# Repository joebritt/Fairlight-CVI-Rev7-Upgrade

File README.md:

# Fairlight-CVI-Rev7-Upgrade
Board set to upgrade a Rev5 Fairlight CVI to Rev7. This upgrade also eliminates the need for backup batteries.

See overview and installation guide [here](https://docs.google.com/document/d/1melksT-DwwU80pforqxVVXWFiSj0hJ2Gdj74KaH-A6M/edit?usp=sharing).

### All PCB designs were done in Eagle.

There are 4 different PCBs:</br>

One is the actual CVI06A, which mounts to the rear of the CVI. It is substantially smaller than the original CVI06.</br>

One is a small board which replaces the SRAM inside the CVI. This new board uses an FRAM to provide nonvolatile storage without a battery</br>

Two of these are just DIP-to-PLCC EPROM adapter boards.</br>
I made these because I had a bunch of PLCC 27C010 EPROMS I wanted to use! You can also just use 2716 and 27C128 EPROMs instead of these boards.

### EPROM Images

There are 4 EPROM images for inside the CVI unit. You'll replace the Rev5 EPROMs with parts programmed with these images:

CVI1R70.BIN and CVI2R70.BIN are images of Rev7 firmware EPROMs CVI1 and CVI2. These each go in a 27C128 16KB EPROM.

CVIHO52.BIN is the Horizonal timing control EPROM. This goes into a 2716 2KB EPROM.</br>
CVIVE50.BIN is the Vertical timing control EPROM. This goes into a 2716 2KB EPROM.

### PCB Designs

[27C128_adapter](https://oshpark.com/shared_projects/G9Li1LrF):</br>
Adapts a PLCC32 27C010 style memory to a DIP 27C128 style memory footprint.
Program just the bottom 16KB of the 27C010 before soldering it to the board.

[2716_adapter](https://oshpark.com/shared_projects/a2X7br2n):</br>
Adapts a PLCC32 27C010 style memory to a DIP 2716 style memory footprint.
Program just the bottom 2KB of the 27C010 before soldering it to the board.

[NoBattNVRAM](https://oshpark.com/shared_projects/FdYXVcIm):</br>
Replaces the CVI SRAM / 3V Lithium battery with FRAM. Nonvolatile memory, no battery needed.
A wire with a grabber clip is used to pick up the 6809 /E clock, which is needed to qualify accesses to the FRAM.

[CVI06A](https://oshpark.com/shared_projects/1o1eqgmB):</br>
The main attraction. Replacement for the original CVI06 expansion board. Smaller, easier to attach, and also uses FRAM for battery-free nonvolatile storage. Program the 27C010 for this board with the CVI43_CVI06A_v11 file in the low 32KB. This image contains the CVI3 and CVI4 Rev7 firmware EPROM images in a single part.

### Enclosure

CVI06A_box.stl and CVI06A_lid.stl can be 3D printed to make a small enclosure to protect the CVI06A PCB.</br>
The box is held together by friction. Note the capture features and line them up when closing.</br>
</br>
You can see the OnShape files used to create the enclosure box [here](https://cad.onshape.com/documents/24956ac0c366857a8c3e2111/w/adee8d27d6b88507ca310e0c/e/6c70102fddee723f7350afbb) and top [here](https://cad.onshape.com/documents/769b7af279cff9270446b3d7/w/f598dc3f7b092dcb1121a7f3/e/3ff1c2d9f7cff27cb58aa0f2).

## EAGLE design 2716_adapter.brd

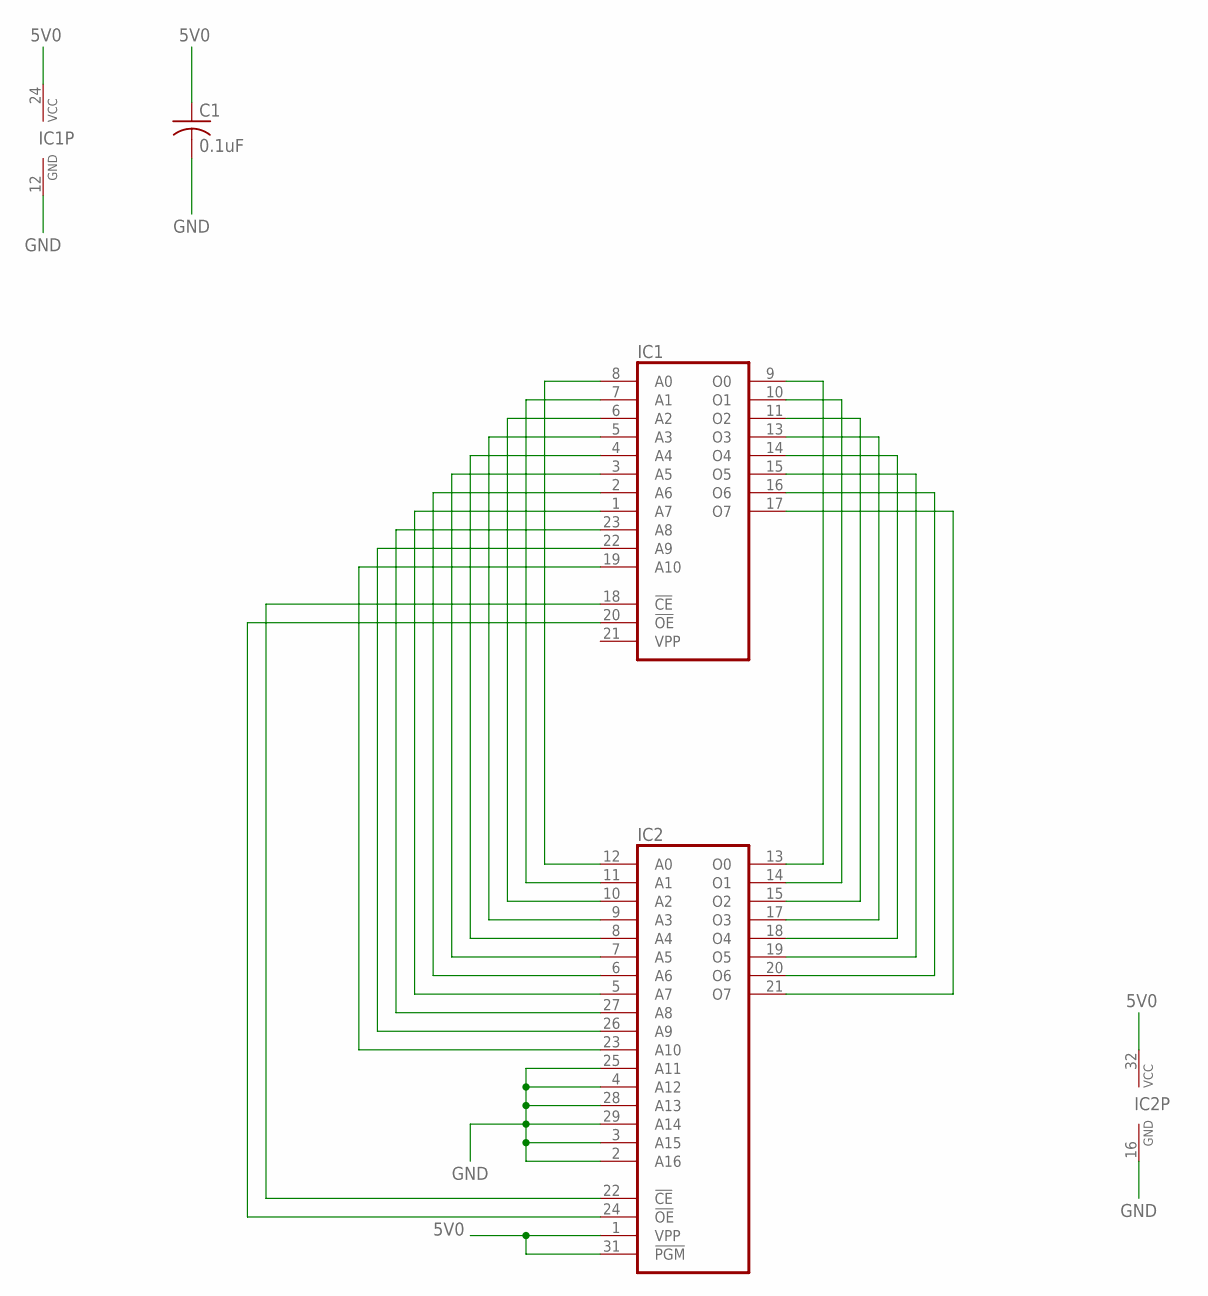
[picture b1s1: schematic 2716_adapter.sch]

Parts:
C1: 0.1uF; C0603K
IC1: 2716; DIL24
IC2: 27010PLCC32; PLCC32R

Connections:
5V0: C1.1, IC1.24 (VCC), IC2.1 (VPP), IC2.31 (!PGM), IC2.32 (VCC)
GND: C1.2, IC1.12 (GND), IC2.2 (A16), IC2.3 (A15), IC2.4 (A12), IC2.16 (GND), IC2.25 (A11), IC2.28 (A13), IC2.29 (A14)
unnamed: IC1.9 (O0), IC2.13 (O0)
unnamed: IC1.10 (O1), IC2.14 (O1)
unnamed: IC1.11 (O2), IC2.15 (O2)
unnamed: IC1.13 (O3), IC2.17 (O3)
unnamed: IC1.14 (O4), IC2.18 (O4)
unnamed: IC1.15 (O5), IC2.19 (O5)
unnamed: IC1.16 (O6), IC2.20 (O6)
unnamed: IC1.17 (O7), IC2.21 (O7)
unnamed: IC1.8 (A0), IC2.12 (A0)
unnamed: IC1.7 (A1), IC2.11 (A1)
unnamed: IC1.6 (A2), IC2.10 (A2)
unnamed: IC1.5 (A3), IC2.9 (A3)
unnamed: IC1.4 (A4), IC2.8 (A4)
unnamed: IC1.3 (A5), IC2.7 (A5)
unnamed: IC1.2 (A6), IC2.6 (A6)
unnamed: IC1.1 (A7), IC2.5 (A7)
unnamed: IC1.23 (A8), IC2.27 (A8)
unnamed: IC1.22 (A9), IC2.26 (A9)
unnamed: IC1.19 (A10), IC2.23 (A10)
unnamed: IC1.18 (!CE), IC2.22 (!CE)
unnamed: IC1.20 (!OE), IC2.24 (!OE)

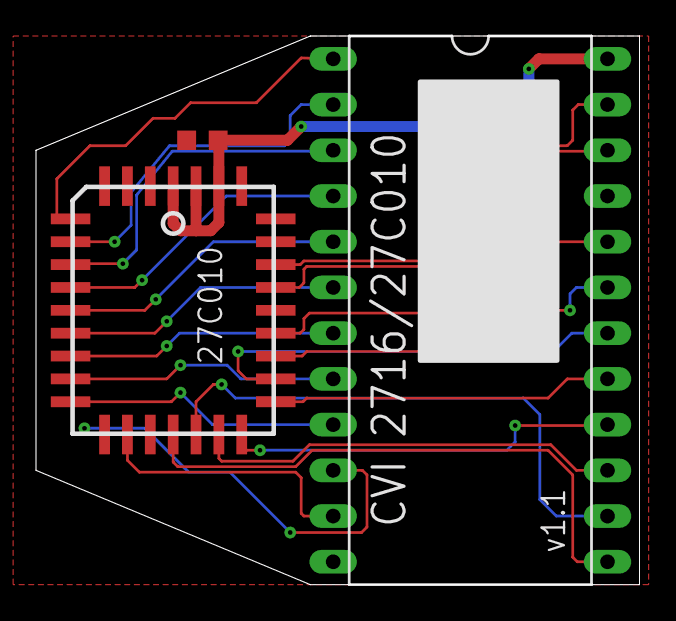
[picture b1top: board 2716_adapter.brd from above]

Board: 2 copper layers, 33.5 x 30.5 mm, 3 parts (0 on the bottom side), 23 nets.

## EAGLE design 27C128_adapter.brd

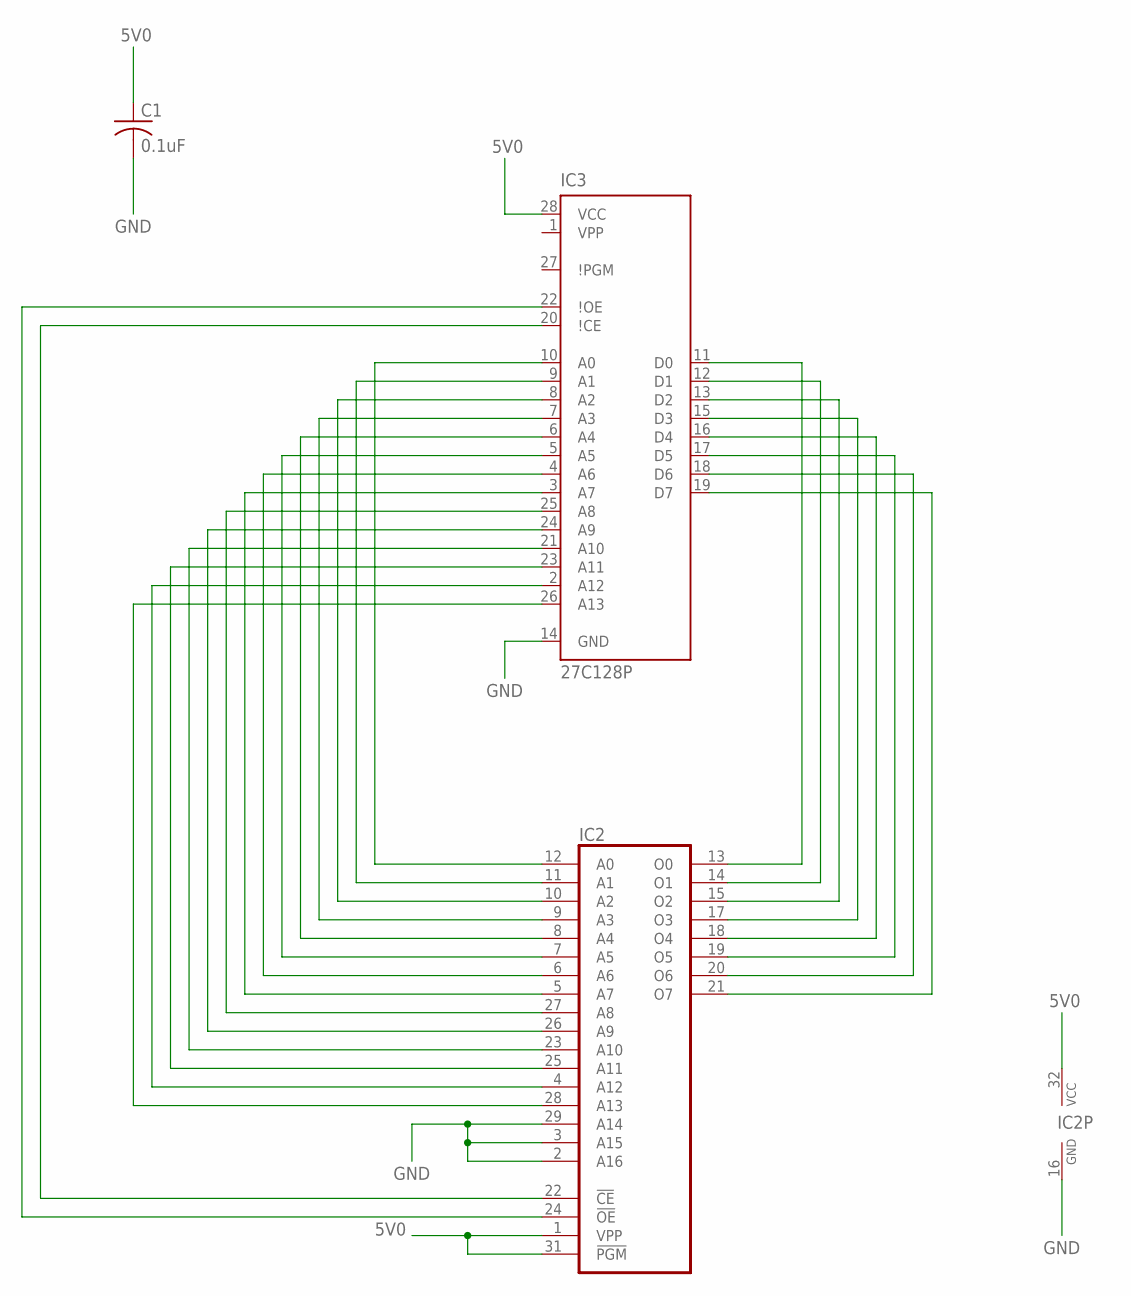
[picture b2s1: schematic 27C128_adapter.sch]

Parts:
C1: 0.1uF; C0603K
IC2: 27010PLCC32; PLCC32R
IC3: 27C128P; DIL28-6

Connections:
5V0: C1.1, IC2.1 (VPP), IC2.31 (!PGM), IC2.32 (VCC), IC3.28 (VCC)
GND: C1.2, IC2.2 (A16), IC2.3 (A15), IC2.16 (GND), IC2.29 (A14), IC3.14 (GND)
unnamed: IC2.25 (A11), IC3.23 (A11)
unnamed: IC2.4 (A12), IC3.2 (A12)
unnamed: IC2.28 (A13), IC3.26 (A13)
unnamed: IC2.17 (O3), IC3.15 (D3)
unnamed: IC2.18 (O4), IC3.16 (D4)
unnamed: IC2.19 (O5), IC3.17 (D5)
unnamed: IC2.20 (O6), IC3.18 (D6)
unnamed: IC2.21 (O7), IC3.19 (D7)
unnamed: IC2.12 (A0), IC3.10 (A0)
unnamed: IC2.11 (A1), IC3.9 (A1)
unnamed: IC2.14 (O1), IC3.12 (D1)
unnamed: IC2.13 (O0), IC3.11 (D0)
unnamed: IC2.15 (O2), IC3.13 (D2)
unnamed: IC2.22 (!CE), IC3.20 (\!CE)
unnamed: IC2.24 (!OE), IC3.22 (\!OE)
unnamed: IC2.10 (A2), IC3.8 (A2)
unnamed: IC2.9 (A3), IC3.7 (A3)
unnamed: IC2.8 (A4), IC3.6 (A4)
unnamed: IC2.7 (A5), IC3.5 (A5)
unnamed: IC2.6 (A6), IC3.4 (A6)
unnamed: IC2.5 (A7), IC3.3 (A7)
unnamed: IC2.27 (A8), IC3.25 (A8)
unnamed: IC2.26 (A9), IC3.24 (A9)
unnamed: IC2.23 (A10), IC3.21 (A10)

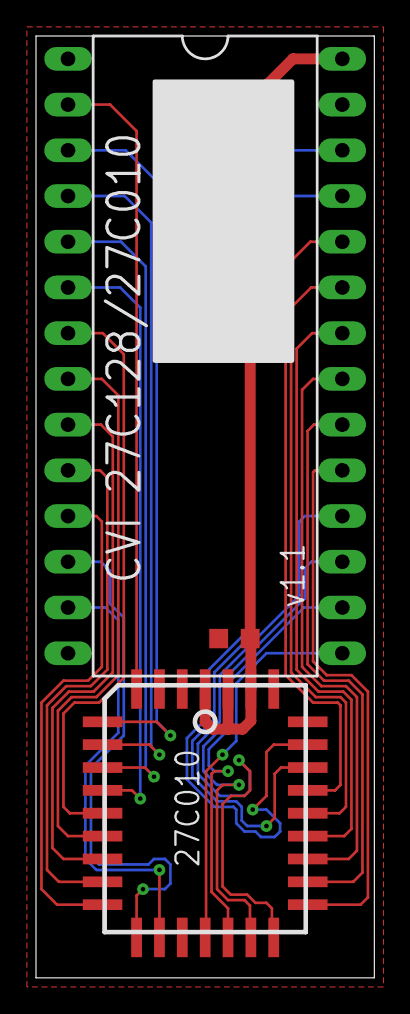
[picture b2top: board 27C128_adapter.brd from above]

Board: 2 copper layers, 18.8 x 52.3 mm, 3 parts (0 on the bottom side), 26 nets.

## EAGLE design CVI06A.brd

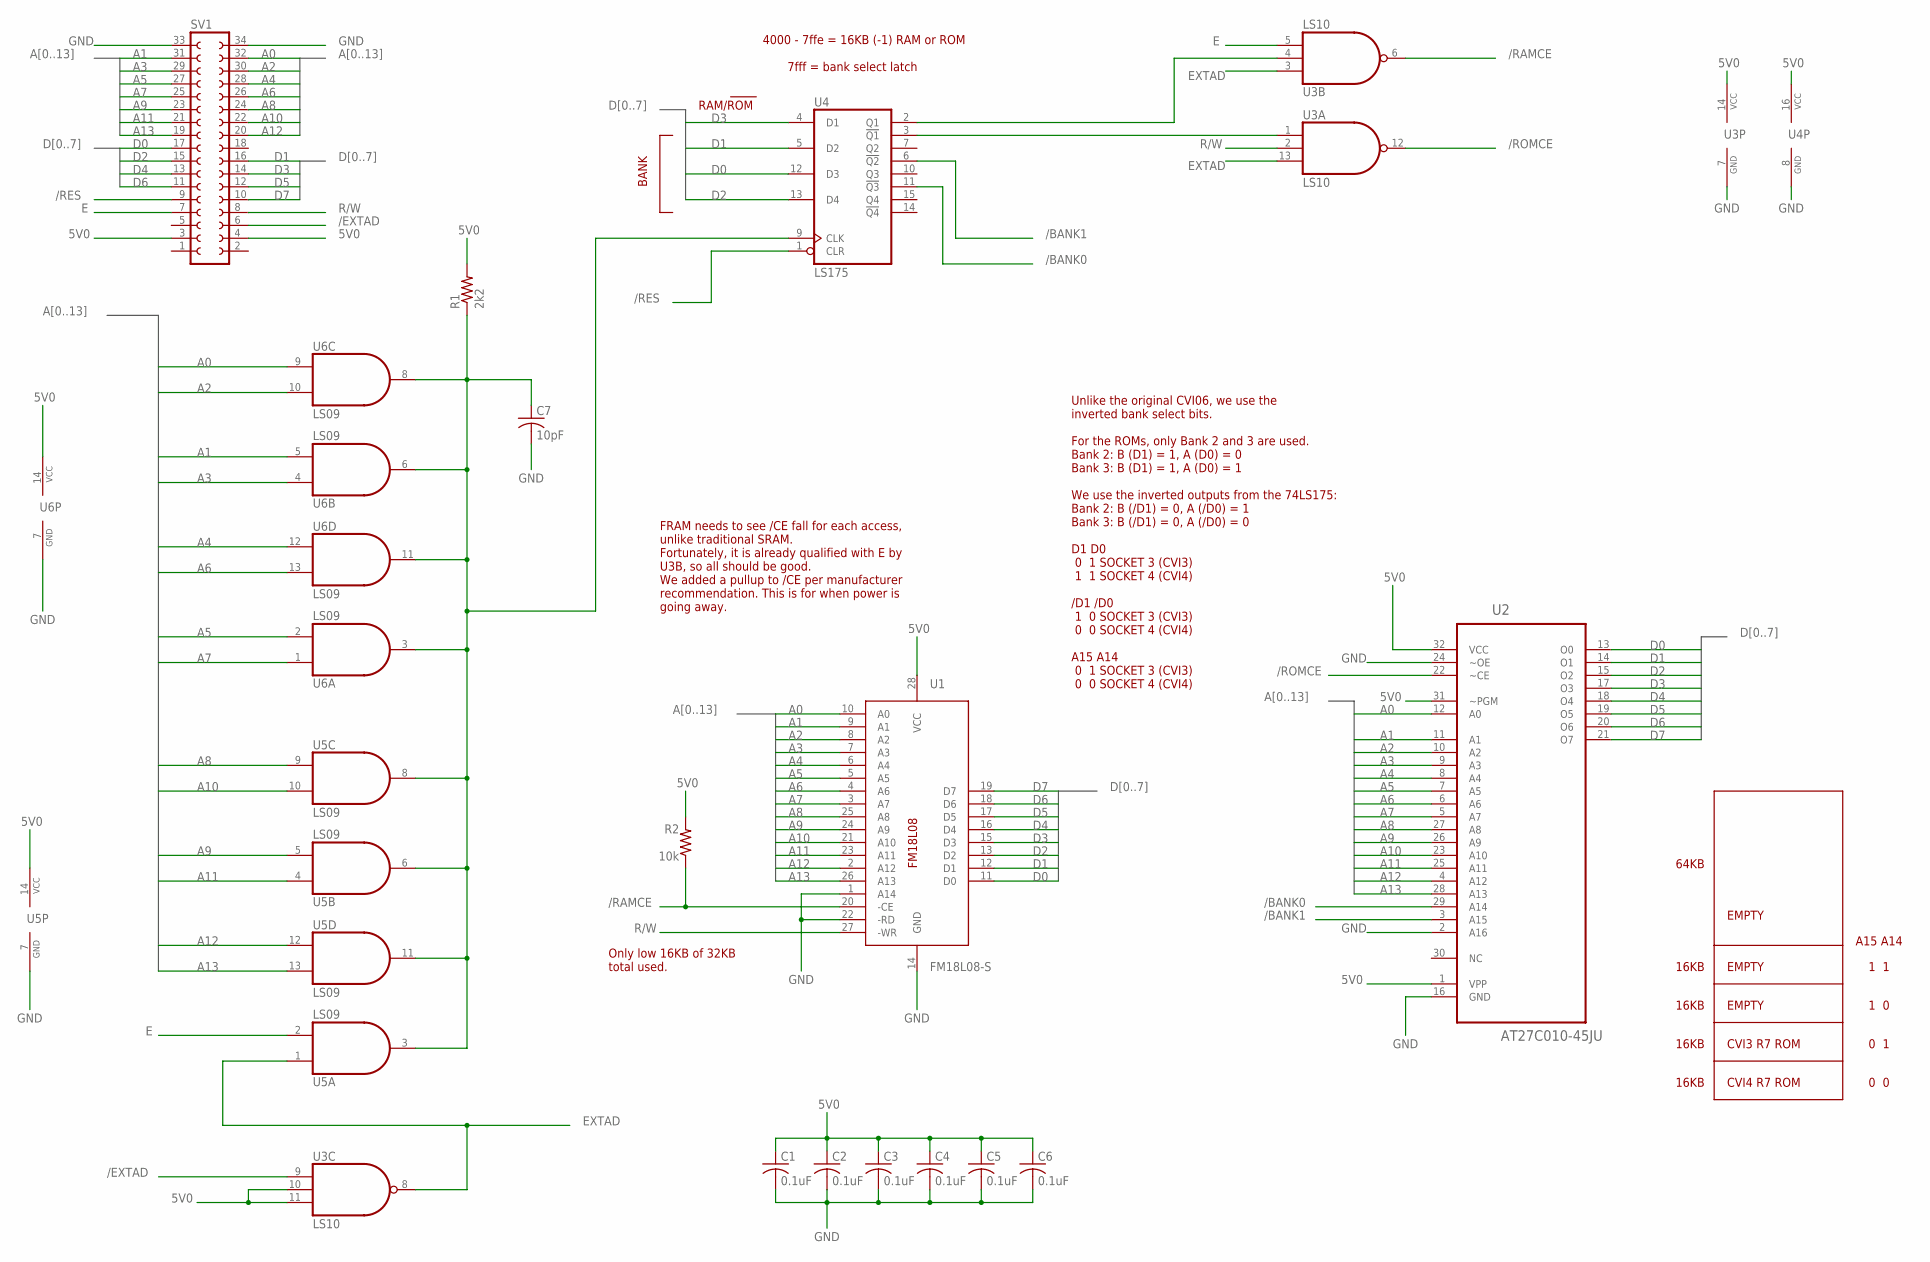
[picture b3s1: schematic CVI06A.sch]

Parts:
C1, C2, C3, C4, C5, C6: 0.1uF; C0603K
C7: 10pF; C0805
R1: 2k2; R0805
R2: 10k; R0805
SV1: FE17-2
U1: FM18L08-S; SO-28W
U2: AT27C010-45JU; PLCC127P1500X1250X355-32N
U3: LS10; SO14
U4: LS175; SO16
U5, U6: LS09; SO14

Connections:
5V0: C1.1, C2.1, C3.1, C4.1, C5.1, C6.1, R1.2, R2.2, SV1.3, SV1.4, U1.28 (VCC), U2.1 (VPP), U2.31 (~PGM), U2.32 (VCC), U3.10 (I1), U3.11 (I2), U3.14 (VCC), U4.16 (VCC), U5.14 (VCC), U6.14 (VCC)
/BANK0: U2.29 (A14), U4.11 (!Q3)
/BANK1: U2.3 (A15), U4.6 (!Q2)
/EXTAD: SV1.6, U3.9 (I0)
/RAMCE: R2.1, U1.20 (-CE), U3.6 (O)
/RES: SV1.9, U4.1 (CLR)
/ROMCE: U2.22 (~CE), U3.12 (O)
A0: SV1.32, U1.10 (A0), U2.12 (A0), U6.9 (I0)
A1: SV1.31, U1.9 (A1), U2.11 (A1), U6.5 (I1)
A2: SV1.30, U1.8 (A2), U2.10 (A2), U6.10 (I1)
A3: SV1.29, U1.7 (A3), U2.9 (A3), U6.4 (I0)
A4: SV1.28, U1.6 (A4), U2.8 (A4), U6.12 (I0)
A5: SV1.27, U1.5 (A5), U2.7 (A5), U6.2 (I1)
A6: SV1.26, U1.4 (A6), U2.6 (A6), U6.13 (I1)
A7: SV1.25, U1.3 (A7), U2.5 (A7), U6.1 (I0)
A8: SV1.24, U1.25 (A8), U2.27 (A8), U5.9 (I0)
A9: SV1.23, U1.24 (A9), U2.26 (A9), U5.5 (I1)
A10: SV1.22, U1.21 (A10), U2.23 (A10), U5.10 (I1)
A11: SV1.21, U1.23 (A11), U2.25 (A11), U5.4 (I0)
A12: SV1.20, U1.2 (A12), U2.4 (A12), U5.12 (I0)
A13: SV1.19, U1.26 (A13), U2.28 (A13), U5.13 (I1)
D0: SV1.17, U1.11 (D0), U2.13 (O0), U4.12 (D3)
D1: SV1.16, U1.12 (D1), U2.14 (O1), U4.5 (D2)
D2: SV1.15, U1.13 (D2), U2.15 (O2), U4.13 (D4)
D3: SV1.14, U1.15 (D3), U2.17 (O3), U4.4 (D1)
D4: SV1.13, U1.16 (D4), U2.18 (O4)
D5: SV1.12, U1.17 (D5), U2.19 (O5)
D6: SV1.11, U1.18 (D6), U2.20 (O6)
D7: SV1.10, U1.19 (D7), U2.21 (O7)
E: SV1.7, U3.5 (I2), U5.2 (I1)
EXTAD: U3.3 (I0), U3.8 (O), U3.13 (I2), U5.1 (I0)
GND: C1.2, C2.2, C3.2, C4.2, C5.2, C6.2, C7.2, SV1.33, SV1.34, U1.1 (A14), U1.14 (GND), U1.22 (-RD), U2.2 (A16), U2.16 (GND), U2.24 (~OE), U3.7 (GND), U4.8 (GND), U5.7 (GND), U6.7 (GND)
unnamed: C7.1, R1.1, U4.9 (CLK), U5.3 (O), U5.6 (O), U5.8 (O), U5.11 (O), U6.3 (O), U6.6 (O), U6.8 (O), U6.11 (O)
unnamed: U3.4 (I1), U4.2 (Q1)
unnamed: U3.1 (I0), U4.3 (!Q1)
R/W: SV1.8, U1.27 (-WR), U3.2 (I1)

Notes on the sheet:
RAM/ROM
BANK
Unlike the original CVI06, we use the inverted bank select bits. For the ROMs, only Bank 2 and 3 are used. Bank 2: B (D1) = 1, A (D0) = 0 Bank 3: B (D1) = 1, A (D0) = 1 We use the inverted outputs from the 74LS175: Bank 2: B (/D1) = 0, A (/D0) = 1 Bank 3: B (/D1) = 0, A (/D0) = 0 D1 D0 0 1 SOCKET 3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
FRAM needs to see /CE fall for each access, unlike traditional SRAM. Fortunately, it is already qualified with E by U3B, so all should be good. We added a pullup to /CE per manufacturer recommendation. This is for when power is going away.
16KB
EMPTY
CVI4 R7 ROM
CVI3 R7 ROM
64KB
Only low 16KB of 32KB total used.
0 0
0 1
1 0
1 1
A15 A14
4000 - 7ffe = 16KB (-1) RAM or ROM 7fff = bank select latch

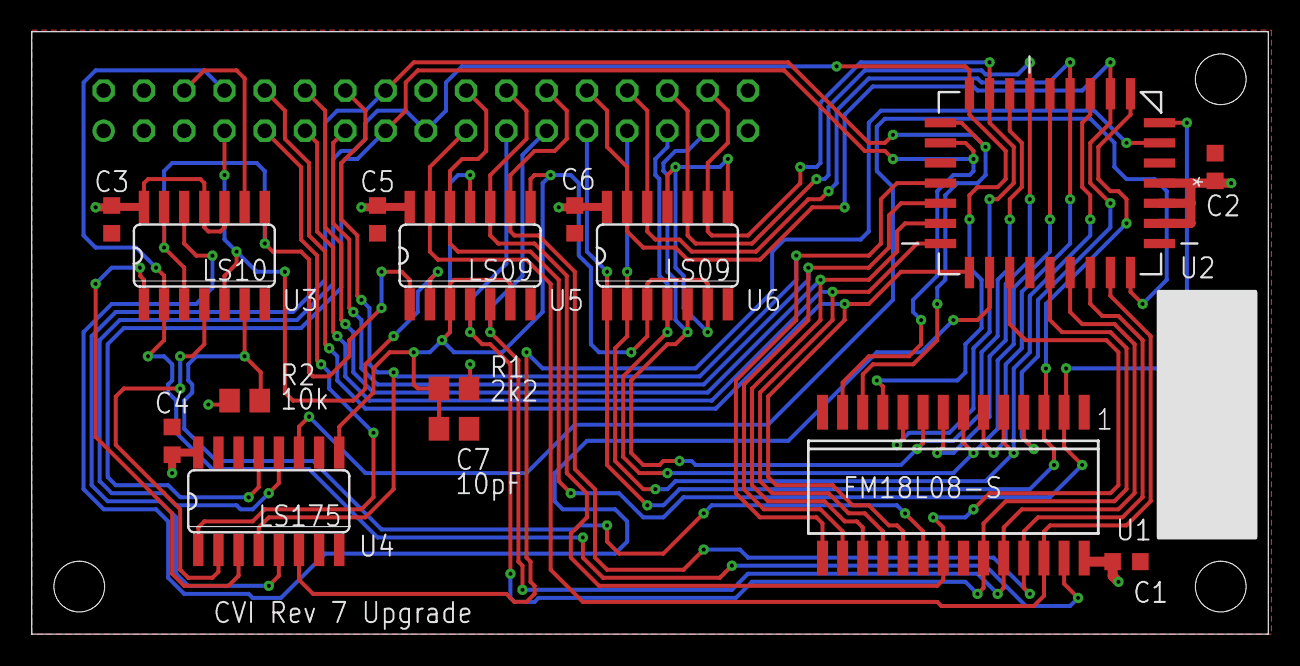
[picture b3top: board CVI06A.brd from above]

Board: 2 copper layers, 78.0 x 38.0 mm, 16 parts (1 on the bottom side), 36 nets.

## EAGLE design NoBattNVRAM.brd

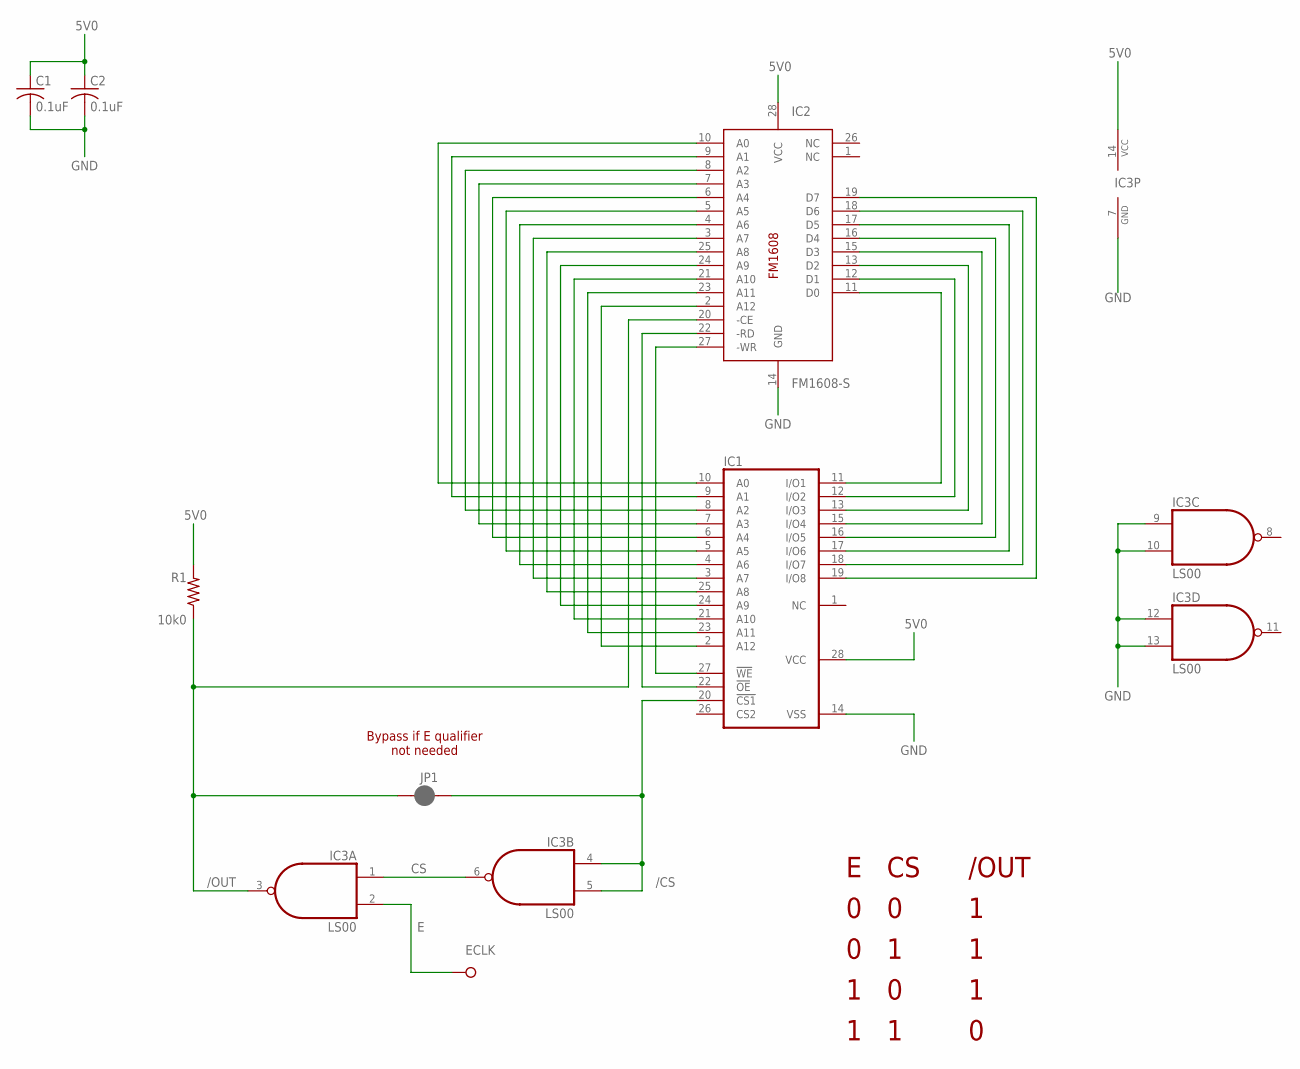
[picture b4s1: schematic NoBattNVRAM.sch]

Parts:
C1, C2: 0.1uF; C0603K
ECLK: JOE-TP-SHORT; JOE-TP-PKG
IC1: 6264A; DIL28-6
IC2: FM1608-S; SO-28W
IC3: LS00; SO14
JP1: JUMPER-PAD-2-NC_BY_PASTENO-SILK; PAD-JUMPER-2-NC_BY_PASTE_NO_SILK
R1: 10k0; R0805

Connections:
5V0: C1.1, C2.1, IC1.28 (VCC), IC2.28 (VCC), IC3.14 (VCC), R1.2
/CS: IC1.20 (!CS1), IC3.4 (I0), IC3.5 (I1), JP1.1
/OUT: IC2.20 (-CE), IC3.3 (O), JP1.2, R1.1
CS: IC3.1 (I0), IC3.6 (O)
E: ECLK.PAD1, IC3.2 (I1)
GND: C1.2, C2.2, IC1.14 (VSS), IC2.14 (GND), IC3.7 (GND), IC3.9 (I0), IC3.10 (I1), IC3.12 (I0), IC3.13 (I1)
unnamed: IC1.10 (A0), IC2.10 (A0)
unnamed: IC1.9 (A1), IC2.9 (A1)
unnamed: IC1.8 (A2), IC2.8 (A2)
unnamed: IC1.7 (A3), IC2.7 (A3)
unnamed: IC1.6 (A4), IC2.6 (A4)
unnamed: IC1.5 (A5), IC2.5 (A5)
unnamed: IC1.4 (A6), IC2.4 (A6)
unnamed: IC1.3 (A7), IC2.3 (A7)
unnamed: IC1.25 (A8), IC2.25 (A8)
unnamed: IC1.24 (A9), IC2.24 (A9)
unnamed: IC1.21 (A10), IC2.21 (A10)
unnamed: IC1.23 (A11), IC2.23 (A11)
unnamed: IC1.2 (A12), IC2.2 (A12)
unnamed: IC1.27 (!WE), IC2.27 (-WR)
unnamed: IC1.22 (!OE), IC2.22 (-RD)
unnamed: IC1.19 (I/O8), IC2.19 (D7)
unnamed: IC1.18 (I/O7), IC2.18 (D6)
unnamed: IC1.17 (I/O6), IC2.17 (D5)
unnamed: IC1.16 (I/O5), IC2.16 (D4)
unnamed: IC1.15 (I/O4), IC2.15 (D3)
unnamed: IC1.13 (I/O3), IC2.13 (D2)
unnamed: IC1.12 (I/O2), IC2.12 (D1)
unnamed: IC1.11 (I/O1), IC2.11 (D0)

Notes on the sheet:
/OUT
Bypass if E qualifier not needed

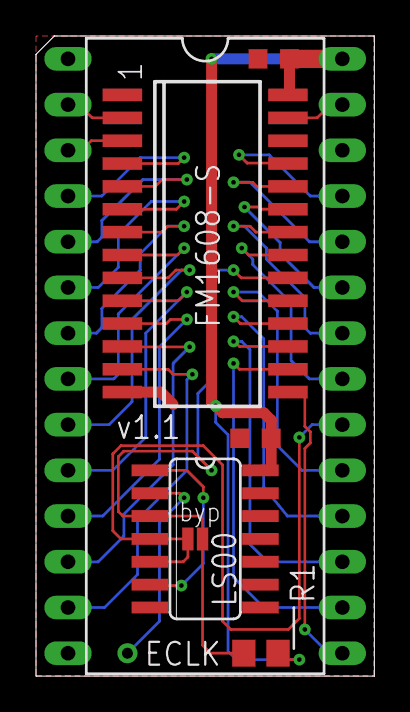
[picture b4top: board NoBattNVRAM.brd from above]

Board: 2 copper layers, 18.8 x 35.6 mm, 8 parts (0 on the bottom side), 29 nets.

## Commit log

2021-07-05 Add files via upload
    Eagle schematics and board layout files for the Fairlight CVI Rev7 upgrade.
    Rev7 EPROM images also included.
2021-07-05 Add files via upload
    PDFs of the 4 board schematics.

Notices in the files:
parts and their libraries:
SparkFun-Passives: Licensing: Creative Commons ShareAlike 4.0 International - https://creativecommons.org/licenses/by-sa/4.0
